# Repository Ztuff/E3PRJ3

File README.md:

E3PRJ3
======

Repo for gruppe 10 til Semesterprojekt 3

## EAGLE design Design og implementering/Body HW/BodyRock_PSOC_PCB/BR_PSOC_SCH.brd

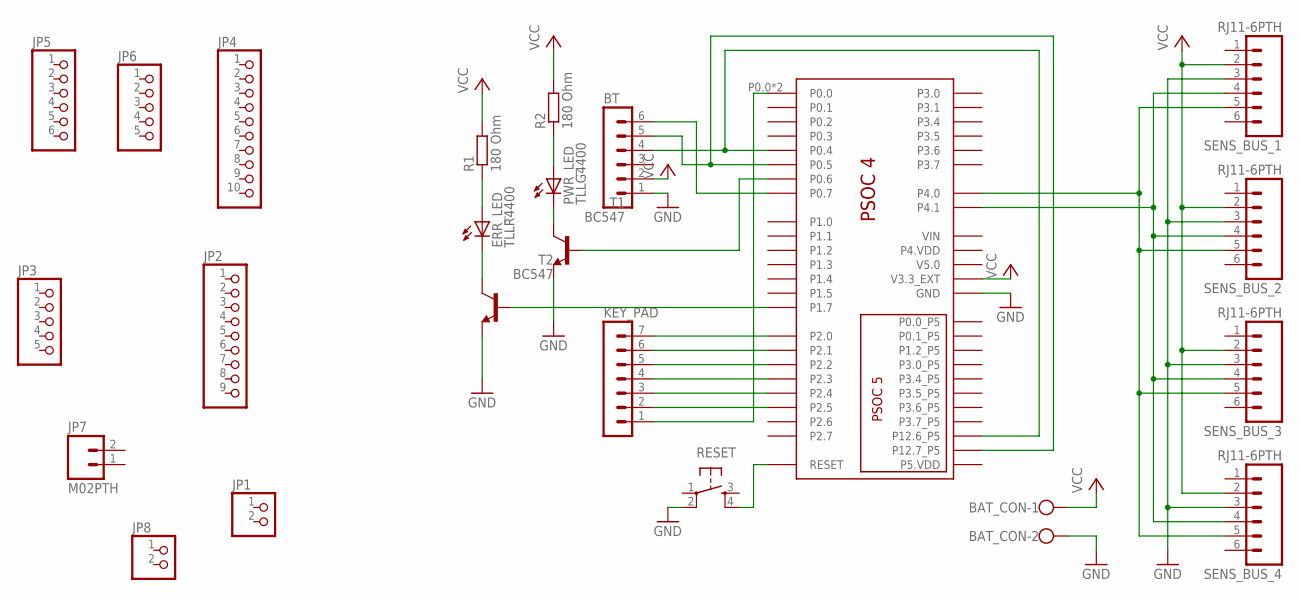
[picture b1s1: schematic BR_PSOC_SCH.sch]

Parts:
BAT_CON: W237-102
BT: MA06-1
ERR_LED: TLLR4400; LED3MM
JP1, JP8: PINHD-1X2; 1X02
JP2: PINHD-1X9; 1X09
JP3, JP6: PINHD-1X5; 1X05
JP4: PINHD-1X10; 1X10
JP5: PINHD-1X6; 1X06
JP7: M02PTH; 1X02
KEY_PAD: MA07-1
PWR_LED: TLLG4400; LED3MM
R1, R2: 180 Ohm; 0204/7
RESET: TAC_SWITCHPTH; TACTILE-PTH
SENS_BUS_1, SENS_BUS_2, SENS_BUS_3, SENS_BUS_4: RJ11-6PTH; RJ11-6
T1, T2: BC547; TO92
U$1: PSOC-4-PIONEER

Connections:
GND: BAT_CON.2, BT.1, RESET.2, SENS_BUS_1.3, SENS_BUS_2.3, SENS_BUS_3.3, SENS_BUS_4.3, T1.1 (E), T2.1 (E), U$1.GND, U$1.GND_2 (GND), U$1.GND_3 (GND), U$1.GND_4 (GND), U$1.GND_5 (GND)
unnamed: RESET.4, U$1.RESET
unnamed: SENS_BUS_1.4, SENS_BUS_2.4, SENS_BUS_3.4, SENS_BUS_4.4, U$1.P4.1
unnamed: SENS_BUS_1.5, SENS_BUS_2.5, SENS_BUS_3.5, SENS_BUS_4.5, U$1.P4.0
unnamed: KEY_PAD.7, U$1.P2.0
unnamed: BT.5, U$1.P0.5, U$1.P12.7_P5
unnamed: BT.4, U$1.P0.4, U$1.P12.6_P5
unnamed: KEY_PAD.6, U$1.P2.1
unnamed: BT.6, U$1.P0.7
unnamed: KEY_PAD.1, U$1.P0.0, U$1.P0.0_2 (P0.0)
unnamed: T2.2 (B), U$1.P1.7
unnamed: KEY_PAD.5, U$1.P2.2
unnamed: KEY_PAD.4, U$1.P2.3
unnamed: KEY_PAD.3, U$1.P2.4
unnamed: KEY_PAD.2, U$1.P2.5
unnamed: T1.2 (B), U$1.P0.6
unnamed: ERR_LED.A, R1.1
unnamed: ERR_LED.K (C), T2.3 (C)
unnamed: PWR_LED.K (C), T1.3 (C)
unnamed: PWR_LED.A, R2.1
VCC: BAT_CON.1, BT.2, R1.2, R2.2, SENS_BUS_1.2, SENS_BUS_2.2, SENS_BUS_3.2, SENS_BUS_4.2, U$1.V3.3_EXT

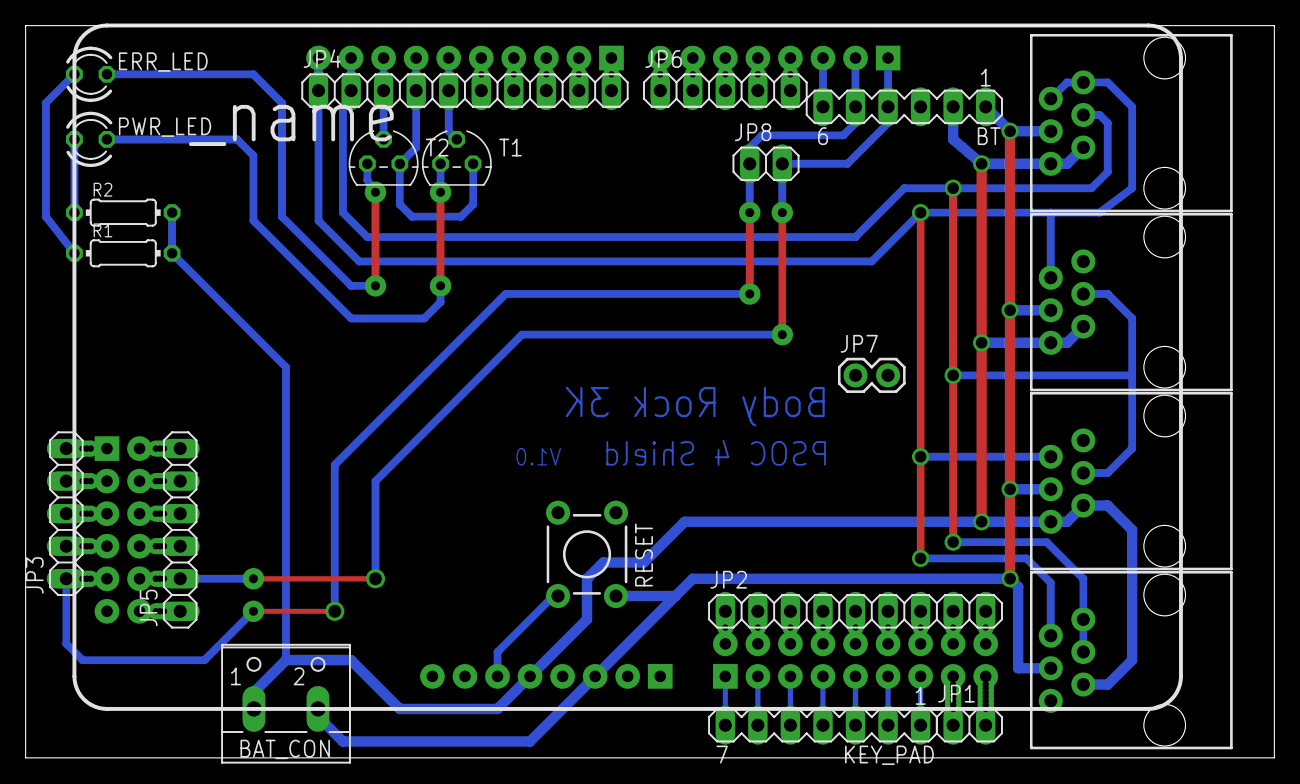
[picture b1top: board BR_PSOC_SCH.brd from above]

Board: 2 copper layers, 97.5 x 57.1 mm, 23 parts (0 on the bottom side), 21 nets.

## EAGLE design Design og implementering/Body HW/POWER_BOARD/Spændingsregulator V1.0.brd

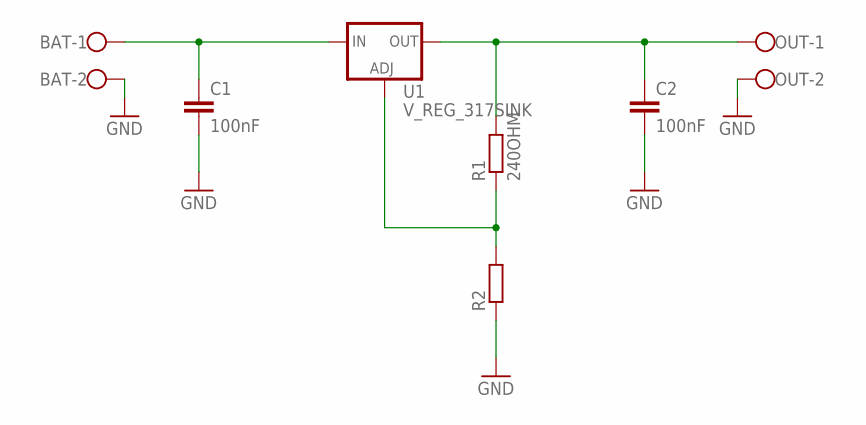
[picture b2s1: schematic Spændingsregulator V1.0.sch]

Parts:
BAT: W237-102
C1, C2: 100nF; C7.5B3
OUT: W237-102
R1: 240OHM; 0204/5
R2: R-EU_0204_5; 0204/5
U1: V_REG_317SINK; TO220-ADJ

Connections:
GND: BAT.2, C1.2, C2.2, OUT.2, R2.1
unnamed: C2.1, OUT.1, R1.2, U1.OUT
unnamed: R1.1, R2.2, U1.ADJ
unnamed: BAT.1, C1.1, U1.IN

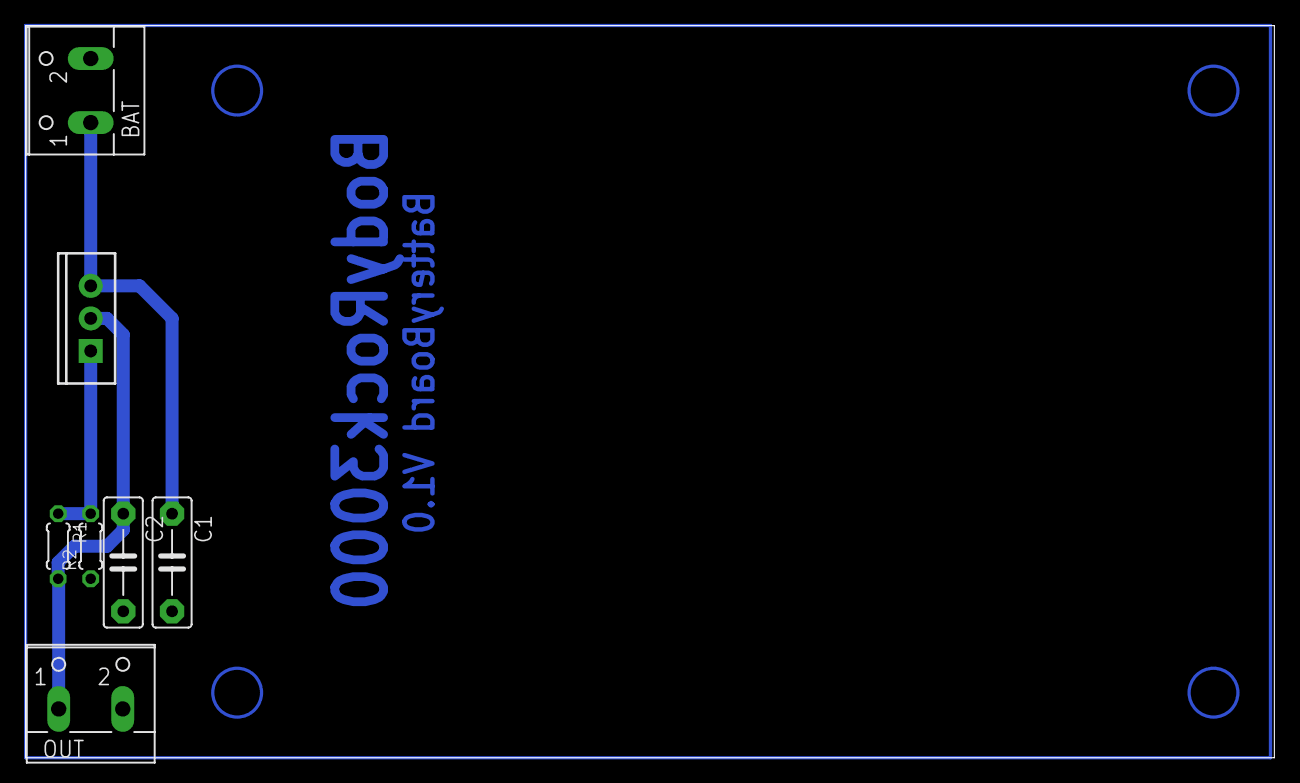
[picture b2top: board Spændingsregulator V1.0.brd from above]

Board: 2 copper layers, 97.5 x 57.1 mm, 7 parts (0 on the bottom side), 4 nets.

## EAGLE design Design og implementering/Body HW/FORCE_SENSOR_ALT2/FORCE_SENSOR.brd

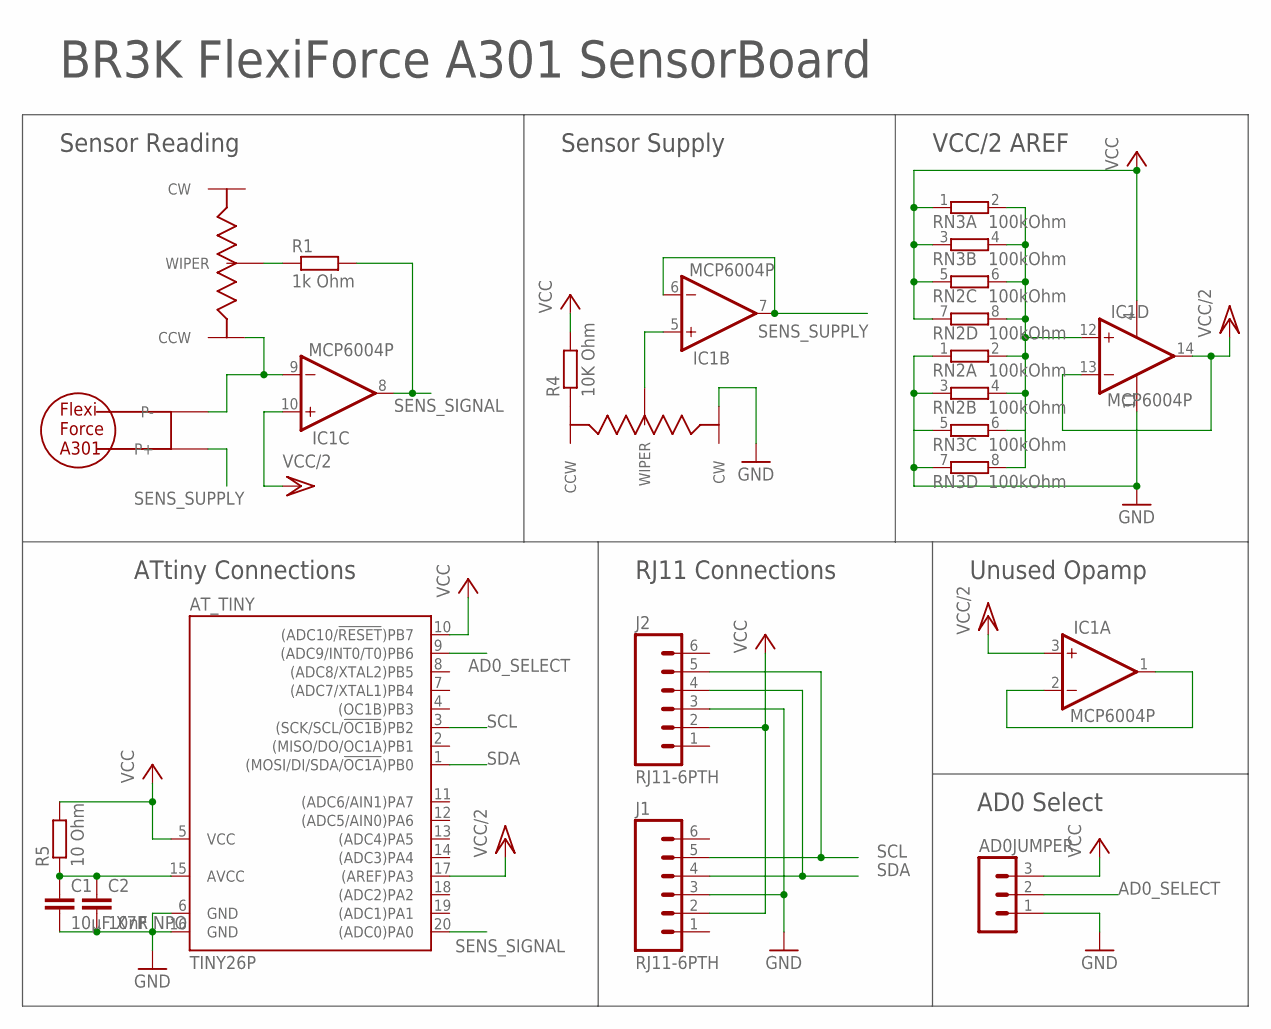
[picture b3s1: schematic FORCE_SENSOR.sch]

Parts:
AD0JUMPER: MA03-1
AT_TINY: TINY26P; DIL20
C1: 10µF X7R; C5B2.5
C2: 10nF NPO; C5B2.5
IC1: MCP6004P; DIL14
J1, J2: RJ11-6PTH; RJ11-6
R1: 1k Ohm; 0207/10
R4: 10K Ohm; 0207/10
R5: 10 Ohm; 0207/10
RN2, RN3: 100kOhm; SIL8
U$1: FLEXI_FORCE_A301; FLEXIFORCE_W237-102
U$2: 100k Ohm; VERT_TRIMPOT
U$3: 10k Ohm; VERT_TRIMPOT

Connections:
AD0_SELECT: AD0JUMPER.2, AT_TINY.9 ((ADC9/INT0/T0)PB6)
GND: AD0JUMPER.1, AT_TINY.6 (GND), AT_TINY.16 (GND), C1.2, C2.2, IC1.11 (V-), J1.3, J2.3, RN2.1, RN2.3 (1), RN3.5 (1), RN3.7 (1), U$3.CW
unnamed: R4.1, U$3.CCW
unnamed: IC1.5 (+IN), U$3.WIP (WIPER)
unnamed: R1.1, U$2.WIP (WIPER)
unnamed: IC1.9 (-IN), U$1.2 (P-), U$2.CCW
unnamed: IC1.1 (OUT), IC1.2 (-IN)
unnamed: AT_TINY.15 (AVCC), C1.1, C2.1, R5.1
unnamed: IC1.12 (+IN), RN2.2, RN2.4 (2), RN2.6 (2), RN2.8 (2), RN3.2, RN3.4 (2), RN3.6 (2), RN3.8 (2)
SCL: AT_TINY.3 ((SCK/SCL/!OC1B!)PB2), J1.5, J2.5
SDA: AT_TINY.1 ((MOSI/DI/SDA/!OC1A!)PB0), J1.4, J2.4
SENS_SIGNAL: AT_TINY.20 ((ADC0)PA0), IC1.8 (OUT), R1.2
SENS_SUPPLY: IC1.6 (-IN), IC1.7 (OUT), U$1.1 (P+)
VCC: AD0JUMPER.3, AT_TINY.5 (VCC), AT_TINY.10 ((ADC10/!RESET!)PB7), IC1.4 (V+), J1.2, J2.2, R4.2, R5.2, RN2.5 (1), RN2.7 (1), RN3.1, RN3.3 (1)
VCC/2: AT_TINY.17 ((AREF)PA3), IC1.3 (+IN), IC1.10 (+IN), IC1.13 (-IN), IC1.14 (OUT)

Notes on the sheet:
ATtiny Connections
RJ11 Connections
Unused Opamp
AD0 Select
Sensor Reading
Sensor Supply
VCC/2 AREF
BR3K FlexiForce A301 SensorBoard

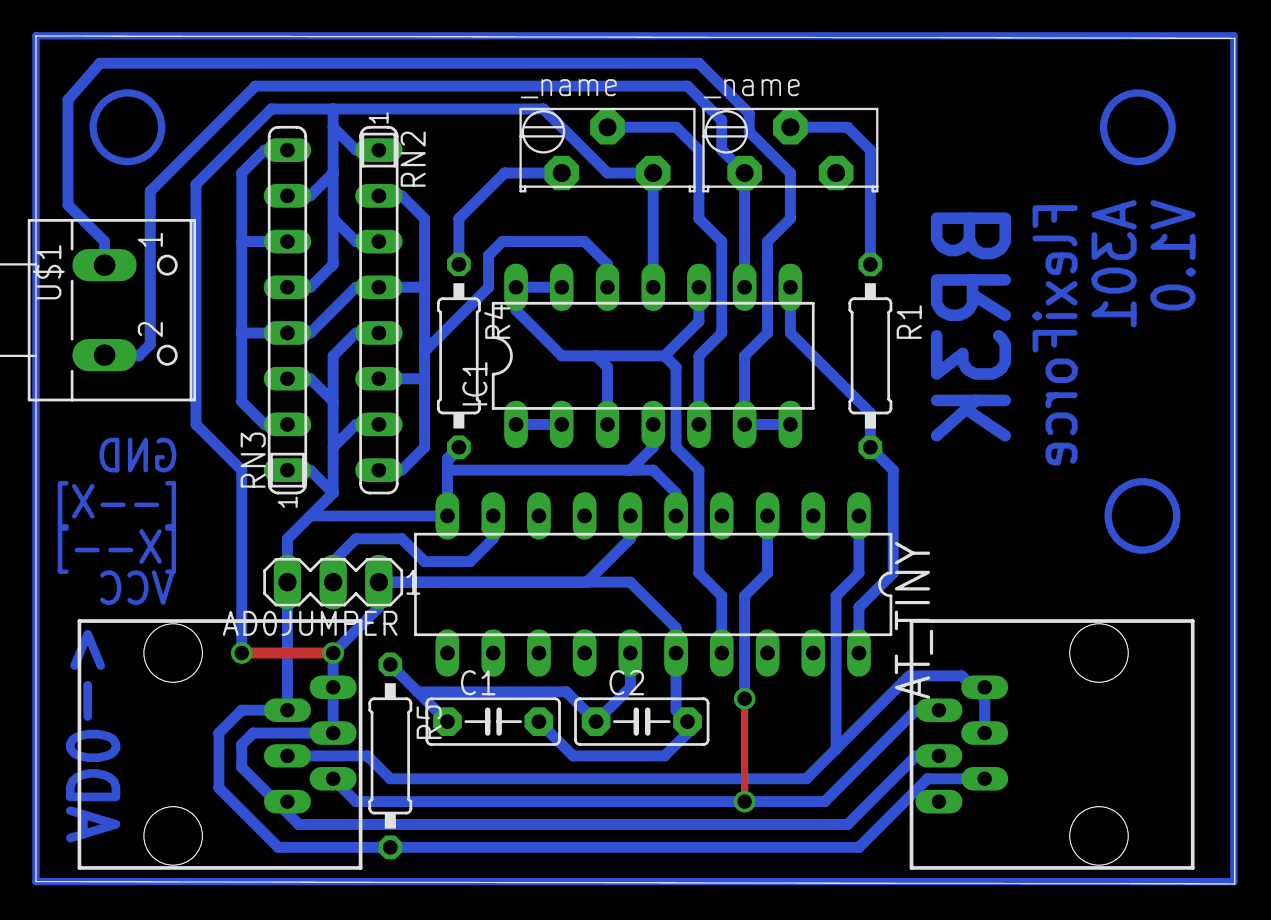
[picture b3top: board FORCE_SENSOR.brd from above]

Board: 2 copper layers, 66.6 x 47.1 mm, 15 parts (0 on the bottom side), 15 nets.

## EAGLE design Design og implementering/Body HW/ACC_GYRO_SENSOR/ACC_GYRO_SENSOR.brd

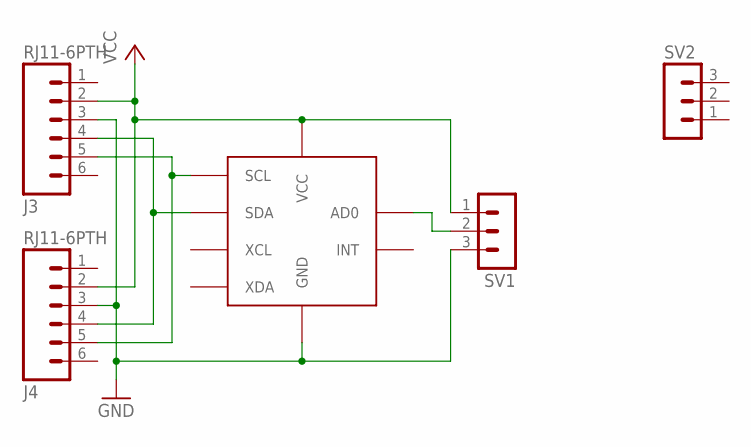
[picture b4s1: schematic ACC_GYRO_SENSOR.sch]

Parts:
J3, J4: RJ11-6PTH; RJ11-6
SV1, SV2: MA03-1
U$1: GY-521

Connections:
GND: J3.3, J4.3, SV1.3, U$1.GND
unnamed: J3.4, J4.4, U$1.SDA
unnamed: J3.5, J4.5, U$1.SCL
unnamed: SV1.2, U$1.AD0
VCC: J3.2, J4.2, SV1.1, U$1.VCC

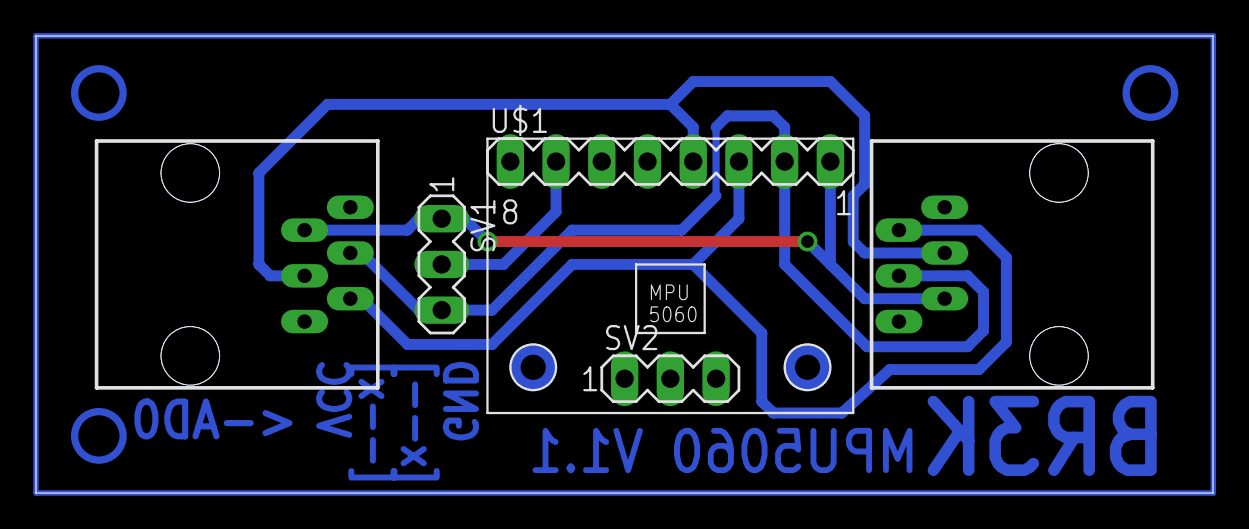
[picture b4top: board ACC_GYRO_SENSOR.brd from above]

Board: 2 copper layers, 65.4 x 25.4 mm, 5 parts (0 on the bottom side), 5 nets.

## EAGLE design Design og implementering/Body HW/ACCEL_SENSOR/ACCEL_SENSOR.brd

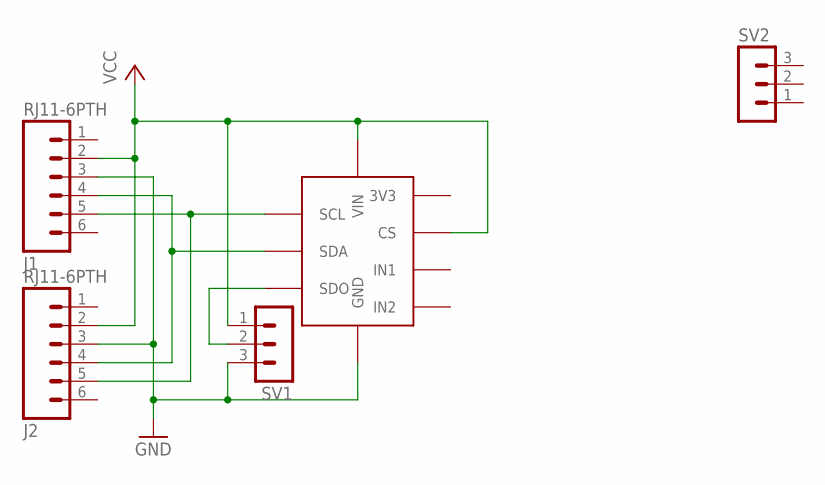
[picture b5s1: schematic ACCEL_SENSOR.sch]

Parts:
J1, J2: RJ11-6PTH; RJ11-6
SV1, SV2: MA03-1
U$1: ADXL345

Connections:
GND: J1.3, J2.3, SV1.3, U$1.GND
unnamed: J1.4, J2.4, U$1.SDA
unnamed: J1.5, J2.5, U$1.SCL
unnamed: SV1.2, U$1.SDO
VCC: J1.2, J2.2, SV1.1, U$1.CS, U$1.VIN

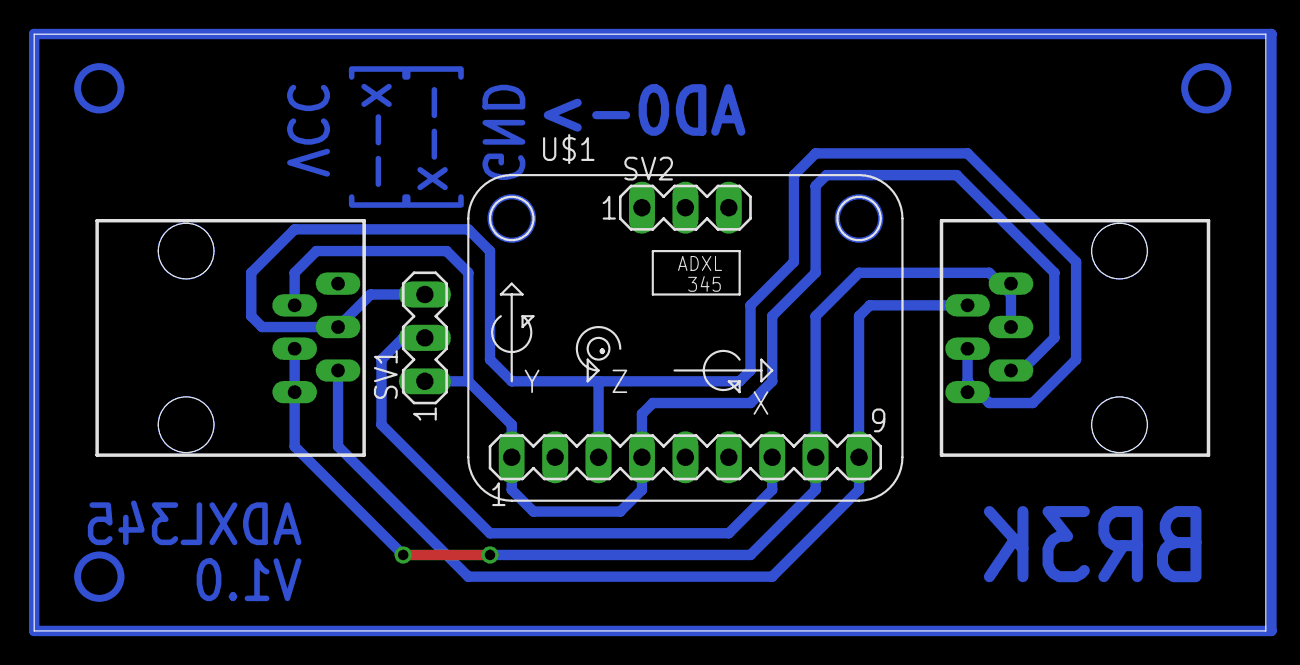
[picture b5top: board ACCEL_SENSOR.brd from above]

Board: 2 copper layers, 72.1 x 34.9 mm, 5 parts (0 on the bottom side), 5 nets.

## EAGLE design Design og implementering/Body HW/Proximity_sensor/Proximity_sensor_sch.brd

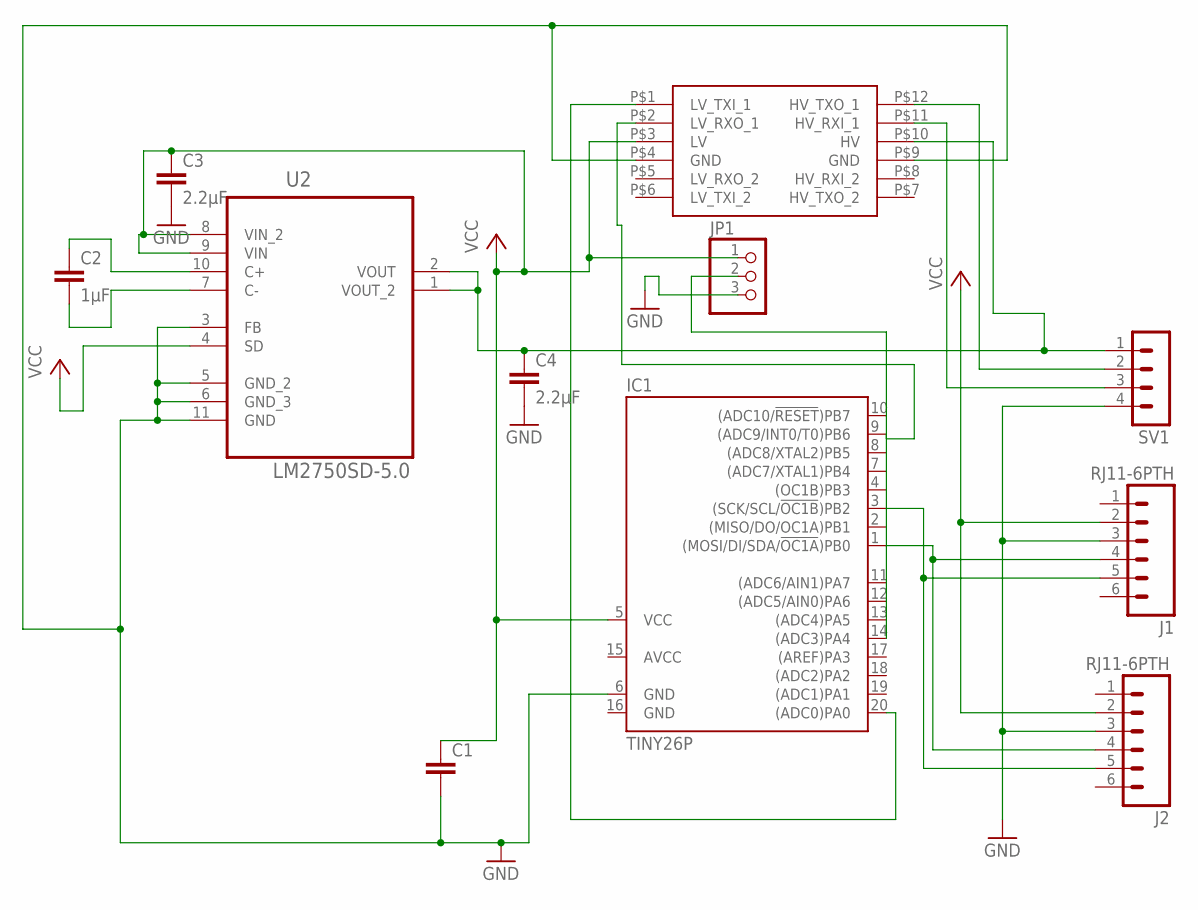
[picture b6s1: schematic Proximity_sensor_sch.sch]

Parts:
C1: C7.5/3; C7.5B3
C2: 1µF; C7.5B3
C3, C4: 2.2µF; C7.5B3
IC1: TINY26P; DIL20
J1, J2: RJ11-6PTH; RJ11-6
JP1: PINHD-1X3; 1X03
SV1: MA04-1
U2: LM2750SD-5.0; DFN300X300X80-11N
U$1: LOGIC_LEVEL_CONVERTER

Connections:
AVCC: IC1.15 (AVCC)
GND: C1.2, C3.2, C4.2, IC1.6 (GND), IC1.16 (GND), J1.3, J2.3, JP1.3, SV1.4, U2.3 (FB), U2.5 (GND_2), U2.6 (GND_3), U2.11 (GND), U$1.P$4 (GND), U$1.P$9 (GND)
unnamed: C4.1, SV1.1, U2.1 (VOUT_2), U2.2 (VOUT), U$1.P$10 (HV)
unnamed: IC1.1 ((MOSI/DI/SDA/!OC1A!)PB0), J1.4, J2.4
unnamed: IC1.3 ((SCK/SCL/!OC1B!)PB2), J1.5, J2.5
unnamed: IC1.20 ((ADC0)PA0), U$1.P$1 (LV_TXI_1)
unnamed: SV1.2, U$1.P$12 (HV_TXO_1)
unnamed: SV1.3, U$1.P$11 (HV_RXI_1)
unnamed: IC1.9 ((ADC9/INT0/T0)PB6), U$1.P$2 (LV_RXO_1)
unnamed: C2.1, U2.10 (C+)
unnamed: C2.2, U2.7 (C-)
unnamed: IC1.14 ((ADC3)PA4), JP1.2
VCC: C1.1, C3.1, IC1.5 (VCC), J1.2, J2.2, JP1.1, U2.4 (SD), U2.8 (VIN_2), U2.9 (VIN), U$1.P$3 (LV)

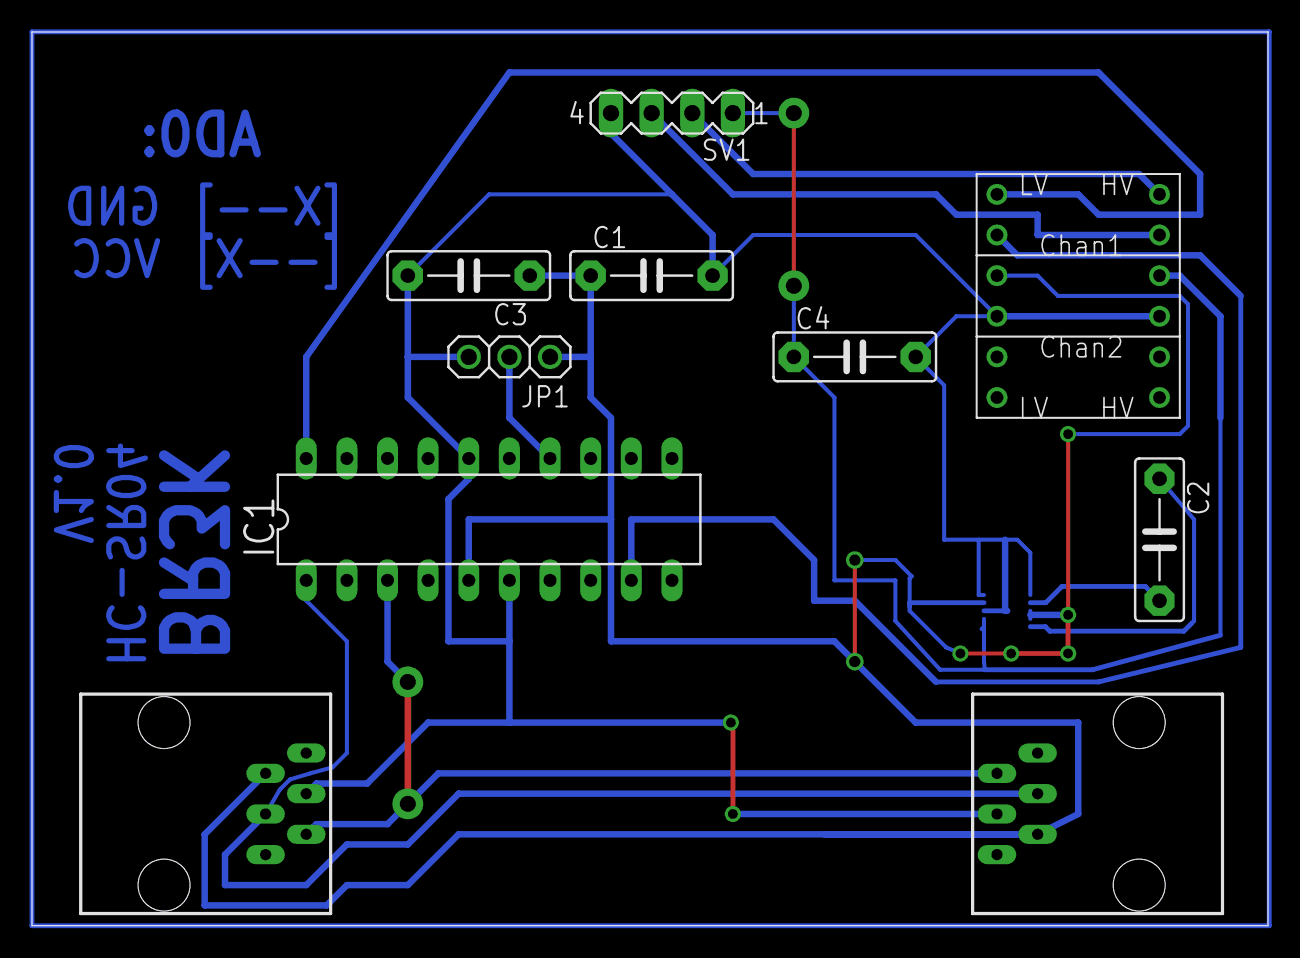
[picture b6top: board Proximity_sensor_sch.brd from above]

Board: 2 copper layers, 77.3 x 55.9 mm, 11 parts (1 on the bottom side), 12 nets.

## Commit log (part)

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2014-10-22 Implementering af objekt orienteret MIDIGen
2014-10-23 har tilføjet filerne til review fra gruppe 8 -Felix
2014-10-23 Noter fra review af vores projekt-dokumentation
2014-10-23 compilation rettelser på linux
2014-10-23 CCAbsGen + CCRelGen skelet nu implementeret
2014-10-24 function protypes for printStrategies()
2014-10-24 Overordnet Skitse til implementering af task 'Main (Controller)'
2014-10-24 Rettelser
2014-10-24 Noter til sysark rettelser
2014-10-24 deleted temp files
2014-10-27 Oprettelse af fil
2014-10-28 Added schematics and board designs for the body HW -Felix
2014-10-29 Manglede 'Preset' og typen på denne
2014-10-29 Funktioner til grænseflade for 'databank' på Rock
2014-10-30 Domain model til Applikationsmodel
2014-10-30 rename af dokument
2014-11-02 Made final changes to eagle designs and exported to gerber -Felix
2014-11-05 Tilføjet FORCE_SENSOR PCB, rettet ACCEL_GYRO_SENSOR -Felix
2014-11-05 Tilrettelse og indføring af Ikke-funktionelle krav i projektrapporten
2014-11-05 Spørgsmål til gruppen efter gruppearbejde på datastrukturen
2014-11-05 System arkitektur arbejde. Klasseidentifikation og -beskrivelse er nu implementerede. Ramme for øvrige SW-arkitektur afsnit også implementeret
2014-11-05 Forsøgt at implementere interrupts
2014-11-07 Indskrivning fra gruppearbejde på tavle
2014-11-07 Ændret databank til datastorage. Men pisse fedt jeg ikke har ændret filnavnet!
2014-11-08 tilføjet Rock gui - Jonas
2014-11-09 Nyttige vejledninger ifm. BT på RPi
2014-11-10 Finished the Force Sensor circuit and sent it and the mpu6050 board for production -Felix
2014-11-10 Info om Raspberry Pi
2014-11-11 Added a folder for the dataStorage implementation as well as a few incomplete .hpp files -Felix
2014-11-11 Opdateret tidsplan
2014-11-12 GUI tilføjelser - Jonas og Mathias
2014-11-14 Grænseflade for ekstern MIDI
    Grænsefladebeskrivelse for MIDI out / ekstern midi
2014-11-16 Systemarkitektur. Rettelse jf. Raspberry Pi samt SD for Body og Fast Lane
2014-11-16 Først og anden udgave af I2C_Slave for Flexiforce 301A
2014-11-17 Nyttige kommandoer på RPi
2014-11-17 Rettelser efter kort internt review
2014-11-17 Tilrettet baud rate fra 9600 til 115200
2014-11-17 Første udkast til Bluetooth på Rock implementeret som klasse
2014-11-18 Implementation of Mapping Scheme Velocity, and CCAbs
2014-11-18 Klassen oprettet, næsten færdig
2014-11-19 Body functions update
2014-11-19 Tilføjet kommandoer til tekstredigering med "vi"
2014-11-20 Header-filer færdige CPP-filer påbegyndt.
2014-11-21 added controller class stub -Felix
2014-11-21 Videreudvikling af funktionerne til main body
2014-11-22 Utestet, men umiddelbart funktionsdygtig BT-klasse. Skal tilpasses projektets behov.
2014-11-22 added a bit to controller class -Felix
2014-11-22 MsgQueue added til GUI
2014-11-22 Bluetooth-klassen til Rpi fungerer nu, og kan kompileres. Dog ikke tilpasset projektets specifikke behov.
2014-11-22 GPIO-connections ifm. BT
2014-11-24 Body main Version 1.0
2014-11-24 Opdateret med dato, Felix og Kristoffer bytter plads som referent
2014-11-24 Opdateret headerfil og .cpp fil for AlsaAdapter.
    Opdateret headerfil og .cpp fl for AlsaAdapter.
    NB: indeholder p.t. en test-main til demonstration. denne fjernes
    snarligt.
2014-11-24 Så er den i pdf version
2014-11-24 Tidsplan update
2014-11-25 Rettet navngivning ift. syntax
2014-11-25 Inkludering af header-filen
2014-11-25 Rettet små syntax-fejl
2014-11-25 Klassenavn ændret fra BTRock til Receiver. Udkommenteret send-funktion, da den ikke skal benyttes. Tilføjet sortering til receive-funktion, mangler at vide hvor hhv. data og preset skal sendes hen
2014-11-26 leviosaaaaaaaaaaaaaaaaa
2014-11-26 SD diagram + beskrivelse Slowlane beskrivelse
2014-11-27 Tilføjet 'axis'-attribut til Sensorkonfiguration. SensorID lavet til int igen, frem for string.
2014-11-27 Mapping Scheme rettelse til channel og command = char
2014-11-27 cpp go hop dil for Midimodule.
2014-11-27 Sender nu data videre i et array af data-structs
2014-11-27 Oprettelse af ændret SensorConfiguration klasse til samarbejde med MidiModule, samt oprettelse i egen hpp og cpp
2014-11-27 opdateret sensorconf cpp og hpp
    opdateret sensorconf cpp og hpp
2014-11-27 opdateret sonsor konf og midimudule
    opdateret sonsor konf og midimudule
2014-11-27 Klargøring af MidiModule test
2014-11-28 SignalIndex fjernet. Et eller andet vector<MidiSignal> tilføjet. SensorConfiguration og SensorConfigurationsbank er splittet ad i to filer.
2014-11-28 Arbejde på MidiModule
2014-11-28 videre arbejde med test til MidiModule
2014-11-28 Cleaned up the Software dir -Felix
2014-11-28 Fix af Felix-feberen
2014-11-28 Qt arbejde med sensor konfigurations ui
2014-11-28 Forsøgt omskrevet til at aflæse sensordata. Driller en del, den aflæser ikke alt, og pakker ikke ID 0 helt rigtigt.
2014-11-29 updated test for MidiModule
2014-11-30 Videre arbejde med projektdokumentation. Indeholder: *Rettet opstilling af kravspecifikation *Nye SW systemarkitektur beskrivelser *Applikationsmodel for MidiModule (mangler beskrivelser)
2014-11-30 Opdateret projektdokumentation med slow lane SD diagram og beskrivelse
2014-11-30 Bare kopieret, og MsgHandler oprettet, mangler noget Qt for at kunne indpasse det
2014-12-01 Version3, data som skal sendes pakkes i 4 forskellige arrays
2014-12-01 Opdateret til kun at håndtere modtagelse af ét ID af gangen. Virker muligvis ikke helt endnu.
2014-12-01 Version 4 af Body Control - Rettet til klasser og sender med frekvens 50 Hz
2014-12-02 Added a solidworks model of a case for the distance sensor - Felix
2014-12-03 opdateret alsaadaper til at modtage en const vector ref
    opdateret alsaadaper til at modtage en const vector ref
2014-12-03 Første udgave af Bluetooth opsætning, teknologiundersøgesel Trådløskommunikation og Projektafgrænsning
2014-12-03 Enhedstest for accelerometer
2014-12-04 Projektrapport skabelon rettelser
2014-12-04 Debug af MidiModule
2014-12-04 MidiModule Test now plays notes from 0-127 in sequence
2014-12-04 ændret channel til 0
2014-12-04 Updated MidiSignal.h - har nu default constructor og benytter std på kkorrekt vis. includes rettede for resterende filer i MidiModule
2014-12-04 Added stl files for the casing for the distance sensor -Felix
2014-12-05 2.udgave af projektafgrænsning 1. udgave af projektgennemførelse 1. udgave af integrationstest af datamodtagelse på Rock og Sensorforsendelse på Body
2014-12-05 Korrekturlæst
2014-12-05 Korrektur
2014-12-05 Temp-fil fjernet
2014-12-06 Første udkast til krav
2014-12-07 Dokumentation for Body implementering
2014-12-08 Beskåret billede af Rock-fladkabel m. forbindelser
2014-12-08 Billeder til modultest af Bluetooth på Rock
2014-12-08 Omdøbt fil og fuldført modultest for Bluetooth på Rock
2014-12-08 Opgaveformulering og udkast til klassediagram
2014-12-09 Første udkast, GUI implementering
2014-12-09 Færdigskitsering af rapportafsnit "fremtidigt arbejde"
2014-12-09 Billede PSoC og HC-05
2014-12-09 Første udkast til funktionsbeskrivelser af body control
2014-12-09 Skabelon til funktionsbeskrivelser
2014-12-09 UML af Body, Rettelse af receiver, sudo kode af Body main
2014-12-09 Rettet småfejl i modultest af BT på Rock
2014-12-09 Modultest af BT på Body er færdig
2014-12-09 Specifikation og analyse mappe-struktur opdatering
2014-12-09 Tilrettelser af 16) "Fremtidigt arbejde", kundeundersøgelse samt tilføjelse af Mapping Scheme krav i Projektdokumentation
2014-12-09 Tilrettelser jf. Dokumentation af MappingScheme
2014-12-10 Fix af gemme-fejl. Æstetisk fix.
2014-12-10 Gui opdateringer - Jonas
2014-12-10 Tilføgejlser til GUI implementering
2014-12-11 Qt arbejde - Jonas
2014-12-11 Dokumentation af MidiSignal samt MidiSignal rettelser
2014-12-11 MidiSignal header rettet
2014-12-11 Flexiforce A301 test and Version 1
2014-12-11 Mapping Scheme and MidiSignal test
2014-12-11 fjernet unødvendige oldParam
2014-12-11 fjernet debug define vedrørende print
2014-12-11 Færdig og flyttet til anden mappe
2014-12-11 Opdateret ATtiny26L mainkode
2014-12-11 MsgHandler skrevet færdig, men ikke testet
2014-12-11 Guide til løsning af problemet med at boote direkte til GUI på Pi
2014-12-11 Udkast til resumé
2014-12-11 Til retning af I2C test dokumenter, bluetooth opsætning mm.
2014-12-12 Mapping Scheme test, rettelser og dokumentation
2014-12-12 Sensordokumentation
2014-12-12 MappingScheme dokumentation færdiggørelse SensorConfiguratino dokumentation påbegyndt SensorConfiguration klasserettelser
2014-12-12 rettelse af kundeundersøgelse
2014-12-12 Beskrivelse af MidiModule
2014-12-12 Flyttet DataBank-afsnittet
2014-12-12 Første udkast til dokumentation Body shield
2014-12-12 test og alsaadapter
2014-12-12 DataBank opdateret
2014-12-12 Controller tilpasset til MsgHandler
2014-12-12 Filer til MsgHandler
2014-12-12 Opdatering af sensordokumentation
2014-12-12 Sletning af ekstra MidiModule mappe i MidiModule
2014-12-12 Fix!
2014-12-12 Projektrapport udkast - elementer mangler
2014-12-12 Indsat HW beskrivelse
2014-12-12 Bluetooth-kommunikation på Receiver opdateret til at fungere!!
2014-12-12 Tilpasset Receiver til at sende videre til midiModule
2014-12-12 FlexiForce SD og SW beskrivelse
2014-12-12 opdatering
2014-12-13 Opdateret projektdokumentation og implementering af Body Control
2014-12-13 Nye beregner af Baudrate sat in i bluetooth opsætning
2014-12-13 Læst korrektur af afsnittene: Krav, Projektgennemførsel, Metoder, Fremtidigt arbejde
2014-12-14 Læst korrektur af afsnit om spændingsforsyning
2014-12-14 Læst korrektur af afsnittet om mapping schemes
2014-12-14 dokumentation af AlsaAdapter
2014-12-14 dokumentation af ALSA
2014-12-14 Opdateret klassen Receiver til at starte en tråd, som modtager data fra Bluetooth ved at kalde receive() i en uendelig løkke.
2014-12-14 V4 af sensordokumentation
2014-12-14 Projektdokumentation opdateret med Receiver
2014-12-14 Dokumentation for Receiver opdateret
2014-12-14 Opdateret projekt dokumentation og rapport
2014-12-14 Opdateret Projektrapport
2014-12-14 Opdateret accepttest_Use_Case_6
2014-12-14 Integrationstest af sensorforsendelser på Body indsat i projektdokumentation
2014-12-14 linuxsampler relaterede filer
2014-12-14 Kom sgu lige til at overwritte Lasses, sorry!
2014-12-14 beskrivelse af kommandoer, der skal inkluderes i /etc/rc.local
2014-12-15 projektrapport
2014-12-15 Gui arbejde
2014-12-15 opdateret afgrænsning
2014-12-15 Mapping Scheme tilrettelse. Afventer test med to akser
2014-12-15 Opdateret ikke funktionelle krav
2014-12-15 tilføjet nye samples til Linuxsampler
2014-12-15 Individuelle konklusioner fra Jeppe, Kristian, Lukas og Kristoffer korrekturlæst og indsat
2014-12-15 Korrekturlæst og indsat individuelle konklusioner fra Lasse og Mathias
2014-12-15 Added a section about the PSoC shield. -Felix
2014-12-15 Sidste funktioner til Body control
2014-12-15 opdatering - Kristian
2014-12-15 To rapport afsnit
2014-12-15 Konklusion færdig
2014-12-15 MappingScheme dokumentation opdatering
2014-12-15 added personal conclusion -Felix
2014-12-15 Projektdokumentation fælles gennemgang til og med Systemarkitektur SW
2014-12-15 Bilag
2014-12-15 Tilføjet Databankens funktioner. Der står ikke så meget andet om Rock SW....? Controlleren fx? :)
2014-12-15 Opdateret projektdokumentation med sidehoved, sidefod og forside
2014-12-15 Tilpasset Receiver i domænemodel i projektdokumentation
2014-12-16 Rettelse af dokumentation
2014-12-16 Bilag HC-SR04
2014-12-16 Projektdokumentation
2014-12-16 Flere bilag sat ind
2014-12-16 Rapport rettet igennem fælles
2014-12-16 Projektdokumentation rettet til side 80
2014-12-16 Opdateret Midimodulbeskrivelse - temp fil
2014-12-16 rettet type til type_ i midimodule klassediagram
2014-12-16 temp fil - opdateret midimodule dokumentation. skal indsættes i endelig doku
2014-12-16 integrationstest fast lane til lyd ud
2014-12-16 Alt rettet, mangler afsnit
2014-12-16 Accepttest færdig
2014-12-16 Bilag 29 og 30
2014-12-16 Bilag sortering
2014-12-16 Started correcting the project report. -Felix
2014-12-16 Bilag oversigt final
2014-12-16 Projektdokumentation streamlinet og accepttest sat ind
2014-12-16 Yderligere rettelser til rapport -Felix
2014-12-16 Indsat et par integrationstests og Mapping scheme, rettet figurnumre og læst korrektur på en del af det
2014-12-16 git log uploadet som .pdf bilag
2014-12-16 Bilag til cd mappe
2014-12-16 Endelig projektrapport
2014-12-16 Til CD
2015-01-19 Projekt Præsentation skabeloner og info
2015-01-20 Fælles powerpoint rettelse + Lukas Disposition til personlig fremlæggelse
2015-01-20 Stuffs disposition til eksamenen
2015-01-21 Referencer jonas

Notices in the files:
parts and their libraries:
SparkFun-Electromechanical: Licensing: Creative Commons ShareAlike 4.0 International - https://creativecommons.org/licenses/by-sa/4.0
